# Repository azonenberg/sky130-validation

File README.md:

# sky130 validation stuff

Right now focusing on OpenRAM bringup chip.

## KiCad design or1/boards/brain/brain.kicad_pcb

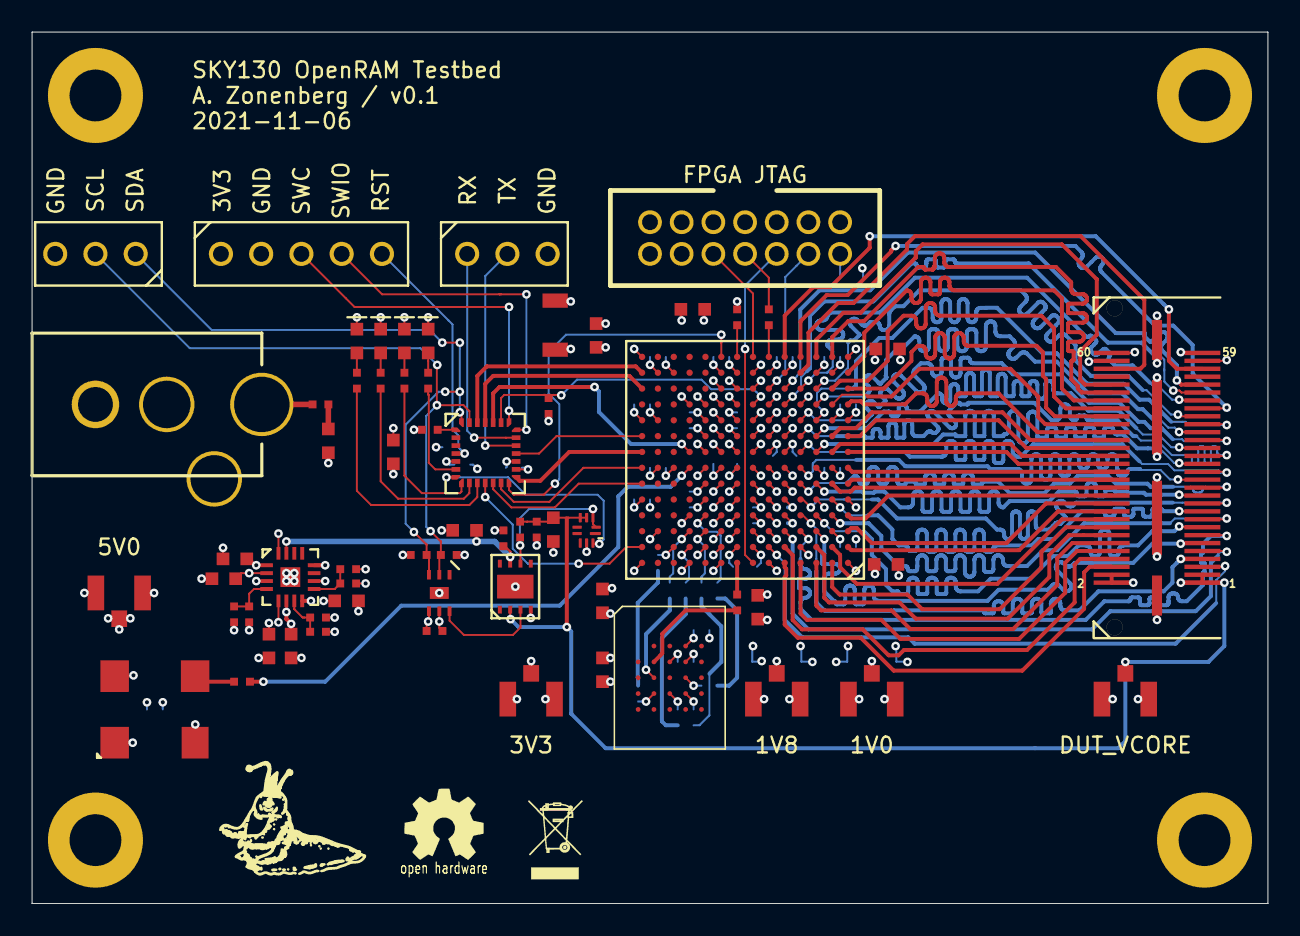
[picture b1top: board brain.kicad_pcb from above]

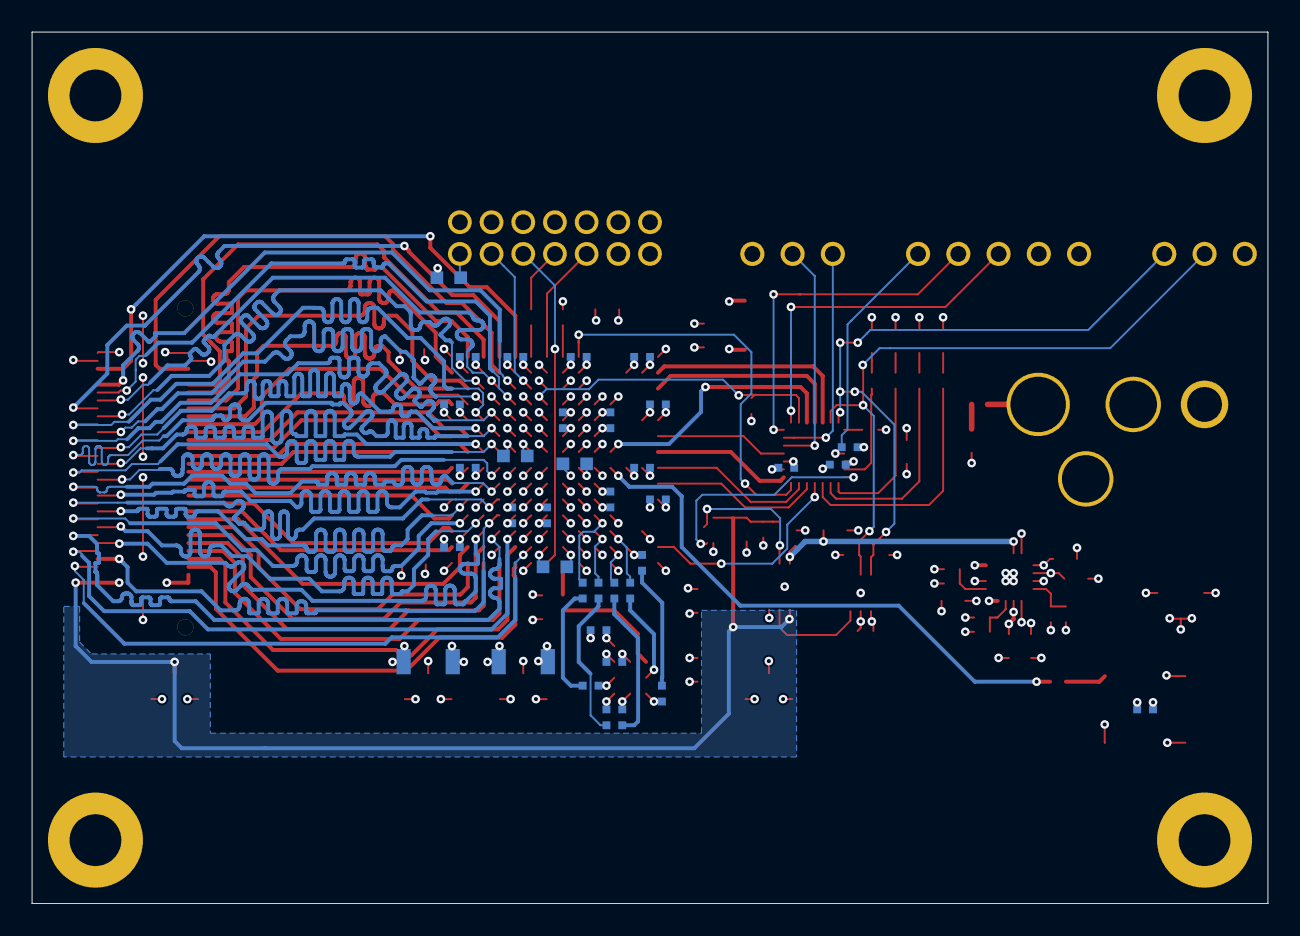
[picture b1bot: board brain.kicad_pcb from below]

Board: 4 copper layers, 78.0 x 55.0 mm, 103 parts (36 on the bottom side), 115 nets.

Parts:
C1, C4: 100 uF; EIA_1206_CAP_NOSILK
C2, C5, C6, C7, C9, C10, C11, C12, C13, C14, C15, C17, C18, C19, C20, C34, C37, C41, C43: 4.7 uF; EIA_0603_CAP_NOSILK
C3: 47 uF; EIA_1206_CAP_NOSILK
C8, C16, C21, C22, C23, C24, C25, C26, C27, C28, C29, C30, C31, C32, C33, C35, C36, C38, C40, C42, C44, C45: 0.47 uF; EIA_0402_CAP_NOSILK
C39: 0.1 uF; EIA_0402_CAP_NOSILK
D1, D2, D3, D4: GREEN; EIA_0603_LED
F1: 1A; EIA_0402_RES_NOSILK
FB1: 600R @ 100 MHz; EIA_0603_INDUCTOR_NOSILK
J1: XILINX_JTAG; XILINX_JTAG_PTH_MOLEX_0878311420
J2: BARREL_JACK; CONN_CUI_PJ-058BH_HIPWR_BARREL_NOSLOT
J3, J6: Conn_01x03; CONN_HEADER_2.54MM_1x3
J4: Conn_01x05; CONN_HEADER_2.54MM_1x5
J5: CONN_SKY130_TEST_HOST; CONN_SAMTEC_QSH-030-01-L-D-A
MH1, MH2, MH3, MH4: SCREWHOLE_4_40; MECHANICAL_CLEARANCEHOLE_4_40
R1, R2: 100K; EIA_0402_RES_NOSILK
R3: 130K; EIA_0402_RES_NOSILK
R4: 49.9K; EIA_0402_RES_NOSILK
R5: 187K; EIA_0402_RES_NOSILK
R6: 33K; EIA_0402_RES_NOSILK
R7, R8, R9, R10, R11, R14, R20, R21, R22, R23, R24, R29: 33; EIA_0402_RES_NOSILK
R12, R25: 10K; EIA_0402_RES_NOSILK
R13, R15, R17, R18: 1K; EIA_0402_RES_NOSILK
R16, R26, R27: 4.7k; EIA_0402_RES_NOSILK
R19: 4.7K; EIA_0402_RES_NOSILK
R28: 10 0.1%; EIA_0402_RES_NOSILK
TP1, TP2, TP3, TP4, TP5: U.FL; CONN_U.FL_TE_1909763-1
U1: STM32F031-QFN28; QFN_28_0.5MM_4x4MM_NOPAD
U2: XC7S15-1FTGB196C; BGA_196_15x15_FULLARRAY_1MM_FTGB196
U3: ADP323; QFN_16_0.5MM_3x3MM
U4: S25FL128SAGBHI300; BGA_24_6x8_DEPOP1_1MM
U5: DAC121C081-WSON; DFN_6_0.65MM_2.2x2.5MM_TI_NGF
U6: ISL24021IRT065Z-T7A‎; DFN_8_0.65MM_3x3MM
U7: INA216A2; QFN_10_0.4MM_1.4x1.8MM_TI_RSW
U8: CB3LV-3C-25M000000; OSCILLATOR_7.0x5.0

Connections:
/1V0: C1.1, C2.1, C6.1, C7.1, C8.1, C15.1, C21.1, C26.1, R1.1, TP4.1, U2.D6, U2.D8, U2.E5, U2.E7, U2.E9, U2.F6, U2.G5, U2.G9, U2.H6, U2.J5, U2.J9, U2.K6, U2.K8, U3.5
/1V8: C3.1, C9.1, C14.1, C16.1, C22.1, R3.1, TP2.1, U2.B8, U2.F8, U2.F10, U2.H10, U2.K10, U2.L9, U3.6
/3V3: C4.1, C10.1, C11.1, C12.1, C17.1, C18.1, C19.1, C20.1, C23.1, C24.1, C25.1, C27.1, C28.1, C29.1, C30.1, C31.1, C32.1, C33.1, C34.1, C35.1, C36.1, C37.1, C38.1, C40.1, C45.1, J1.2, J4.1, J5.57, J5.58, J5.59, J5.60, R5.1, R12.2, R16.1, R19.1, R26.1, R27.1, TP3.1, U1.5, U1.17, U2.B10, U2.G2, U2.G13, U2.K2, U2.K13, U2.M7, U2.N2, U2.N6, U2.N7, U2.N8, U2.N13, U3.8, U4.B4, U5.5, U8.1, U8.4
/DUT socket/ADDR0_0: J5.44, U2.M1
/DUT socket/ADDR0_1: J5.43, U2.M3
/DUT socket/ADDR0_2: J5.41, U2.K3
/DUT socket/ADDR0_3: J5.39, U2.L3
/DUT socket/ADDR0_4: J5.37, U2.K4
/DUT socket/ADDR0_5: J5.35, U2.J3
/DUT socket/ADDR0_6: J5.33, U2.J4
/DUT socket/ADDR0_7: J5.31, U2.H3
/DUT socket/ADDR1_0: J5.13, U2.C4
/DUT socket/ADDR1_1: J5.11, U2.C3
/DUT socket/ADDR1_2: J5.9, U2.C5
/DUT socket/ADDR1_3: J5.7, U2.D4
/DUT socket/ADDR1_4: J5.5, U2.B6
/DUT socket/ADDR1_5: J5.8, U2.B5
/DUT socket/ADDR1_6: J5.12, U2.A3
/DUT socket/ADDR1_7: J5.16, U2.A2
/DUT socket/CLK0: J5.45, U2.P4
/DUT socket/CLK1: J5.55, U2.P5
/DUT socket/CS0_N: J5.46, U2.M2
/DUT socket/CS1_N: J5.56, U2.N4
/DUT socket/DIN0_0: J5.40, U2.L1
/DUT socket/DIN0_1: J5.38, U2.J2
/DUT socket/DIN0_2: J5.32, U2.H1
/DUT socket/DIN0_3: J5.30, U2.G1
/DUT socket/DIN0_4: J5.26, U2.F2
/DUT socket/DIN0_5: J5.22, U2.C1
/DUT socket/DIN0_6: J5.18, U2.B2
/DUT socket/DIN0_7: J5.10, U2.A4
/DUT socket/DOUT0_0: J5.36, U2.J1
/DUT socket/DOUT0_1: J5.42, U2.L2
/DUT socket/DOUT0_2: J5.34, U2.H2
/DUT socket/DOUT0_3: J5.28, U2.F1
/DUT socket/DOUT0_4: J5.24, U2.D1
/DUT socket/DOUT0_5: J5.20, U2.B1
/DUT socket/DOUT0_6: J5.14, U2.B3
/DUT socket/DOUT0_7: J5.6, U2.A5
/DUT socket/DOUT1_0: J5.15, U2.D3
/DUT socket/DOUT1_1: J5.27, U2.G4
/DUT socket/DOUT1_2: J5.29, U2.H4
/DUT socket/DOUT1_3: J5.17, U2.D2
/DUT socket/DOUT1_4: J5.19, U2.E2
/DUT socket/DOUT1_5: J5.21, U2.E4
/DUT socket/DOUT1_6: J5.23, U2.F3
/DUT socket/DOUT1_7: J5.25, U2.F4
/DUT socket/GPIO0: J5.52, U2.P3
/DUT socket/WE0_N: J5.50, U2.P2
/DUT socket/WMASK0_0: J5.51, U2.M5
/DUT socket/WMASK0_1: J5.49, U2.L5
/DUT socket/WMASK0_2: J5.47, U2.M4
/DUT socket/WMASK0_3: J5.48, U2.N1
/DUT_VCORE: C43.1, C44.1, J5.1, J5.2, J5.3, J5.4, R28.1, TP5.1, U6.2, U7.4, U7.5
/DUT_VDD_ISENSE: U1.7, U7.10
/FLASH_CS_N: R11.2, U4.C2
/FLASH_DQ0: R7.2, R21.1
/FLASH_DQ1: R8.2, R22.1
/FLASH_DQ2: R9.2, R23.1
/FLASH_DQ3: R10.2, R24.1
/FLASH_RST_N: R12.1, U4.A4
/FLASH_SCK: R20.1, U4.B2
/FPGA_CLK_25MHZ: R29.1, U2.G11
/FPGA_DONE: U1.14, U2.P9
/FPGA_RST_N: R16.2, U1.23, U2.L7
/GND: C1.2, C2.2, C3.2, C4.2, C5.2, C6.2, C7.2, C8.2, C9.2, C10.2, C11.2, C12.2, C13.2, C14.2, C15.2, C16.2, C17.2, C18.2, C19.2, C20.2, C21.2, C22.2, C23.2, C24.2, C25.2, C26.2, C27.2, C28.2, C29.2, C30.2, C31.2, C32.2, C33.2, C34.2, C35.2, C36.2, C37.2, C38.2, C39.2, C40.2, C41.2, C42.2, C43.2, C44.2, C45.2, D1.1, D2.1, D3.1, D4.1, J1.3, J1.5, J1.7, J1.9, J1.11, J2.2, J3.3, J4.2, J5.GND, J6.3, R2.1, R4.1, R6.1, R25.2, TP1.2, TP2.2, TP3.2, TP4.2, TP5.2, U1.16, U2.A1, U2.A6, U2.A9, U2.A11, U2.A14, U2.B4, U2.B7, U2.B9, U2.C2, U2.C6, U2.C7, U2.C8, U2.C9, U2.C13, U2.D5, U2.D7, U2.D9, U2.D11, U2.E1, U2.E3, U2.E6, U2.E8, U2.E10, U2.E14, U2.F5, U2.F7, U2.F9, U2.G3, U2.G6, U2.G7, U2.G8, U2.G10, U2.G12, U2.H5, U2.H7, U2.H8, U2.H9, U2.J6, U2.J7, U2.J8, U2.J10, U2.K1, U2.K5, U2.K7, U2.K9, U2.K14, U2.L4, U2.L6, U2.L8, U2.L10, U2.L11, U2.M8, U2.M9, U2.N3, U2.N5, U2.N9, U2.N12, U2.P1, U2.P14, U3.12, U3.PAD, U4.B3, U5.4, U5.PAD, U6.4, U6.PAD, U7.9, U8.2
/I2C_SCL: J6.2, R26.2, U1.27, U5.2
/I2C_SDA: J6.1, R27.2, U1.28, U5.3
/JTAG_TCK: J1.6, U2.A7
/JTAG_TDI: J1.10, U2.P7
/JTAG_TDO: J1.8, R14.2
/JTAG_TMS: J1.4, U2.M6
/MCU_GPIO0: U1.12, U2.F14
/MCU_GPIO1: U1.13, U2.G14
/MCU_GPIO2: U1.18, U2.J14
/MCU_GPIO3: U1.11, U2.B14
/MCU_LED0: R13.2, U1.10
/MCU_LED1: R15.2, U1.9
/MCU_LED2: R17.2, U1.8
/MCU_LED3: R18.2, U1.6
/MCU_RST_N: C39.1, J4.5, U1.4
/MCU_SPI_CS_N: U1.15, U2.H14
/MCU_SPI_SCK: U1.24, U2.H11
/MCU_SPI_SI: U1.26, U2.N14
/MCU_SPI_SO: U1.25, U2.M14
/Power supply/5V0: C5.1, C13.1, C41.1, C42.1, FB1.2, TP1.1, U3.1, U3.2, U3.3, U3.10, U3.15, U3.16, U6.7
/Power supply/DAC_VOUT: U5.6, U6.3
/Power supply/DUT_VDD_RAW: R28.2, U6.6, U7.2, U7.3
/Power supply/MCU_BOOT0: R25.1, U1.1
/SWCLK: J4.3, U1.22
/SWDIO: J4.4, U1.21
/UART_RX: J3.1, U1.20
/UART_TX: J3.2, U1.19
unnamed: D1.2, R13.1
unnamed: D2.2, R15.1
unnamed: D3.2, R17.1
unnamed: D4.2, R18.1
unnamed: F1.1, J2.1
unnamed: F1.2, FB1.1
unnamed: R1.2, R2.2, U3.4
unnamed: R3.2, R4.2, U3.7
unnamed: R5.2, R6.2, U3.9
unnamed: R7.1, U2.B11
unnamed: R8.1, U2.B12
unnamed: R9.1, U2.D10
unnamed: R10.1, U2.C10
unnamed: R11.1, U2.C11
unnamed: R14.1, U2.P6
unnamed: R19.2, U2.P8
unnamed: R20.2, U2.A8
unnamed: R21.2, U4.D3
unnamed: R22.2, U4.D2
unnamed: R23.2, U4.C4
unnamed: R24.2, U4.D4
unnamed: R29.2, U8.3

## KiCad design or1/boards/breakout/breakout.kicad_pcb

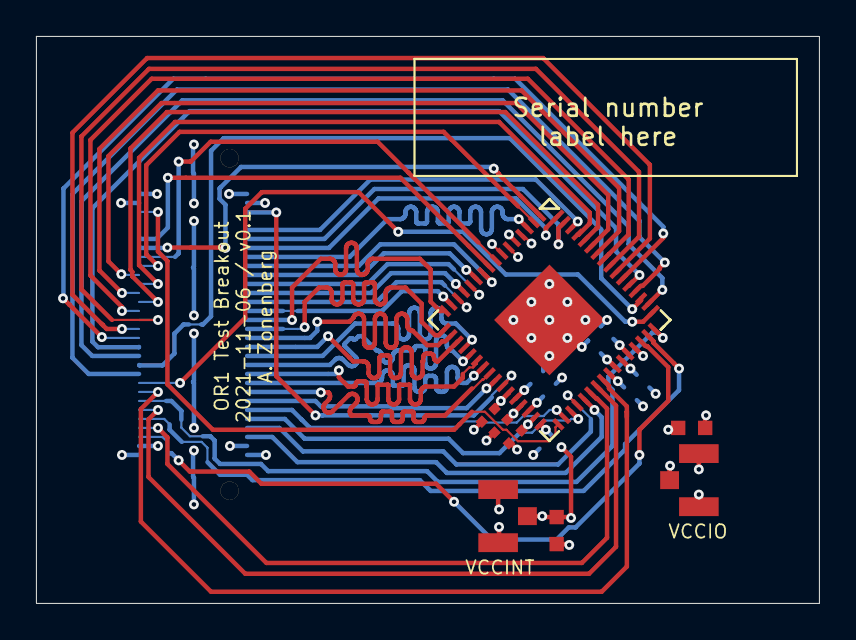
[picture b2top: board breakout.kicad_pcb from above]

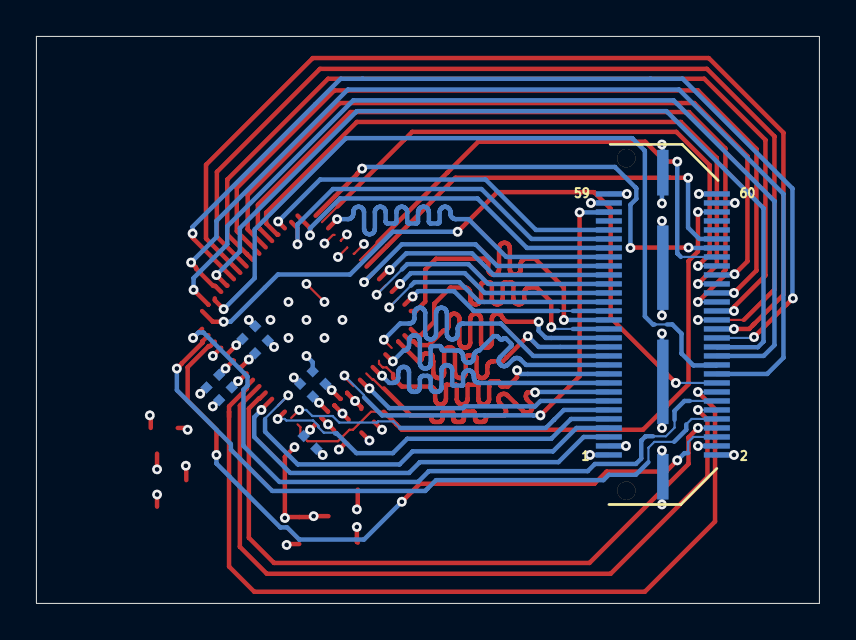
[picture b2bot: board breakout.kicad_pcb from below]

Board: 4 copper layers, 43.5 x 31.5 mm, 16 parts (8 on the bottom side), 52 nets.

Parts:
C1, C2: 4.7 uF; EIA_0603_CAP_NOSILK
C3, C4, C5, C6, C7, C8, C9, C10, C11, C12: 0.47 uF; EIA_0402_CAP_NOSILK
J1: CONN_SKY130_TEST_DEVICE; CONN_SAMTEC_QTH-030-01-L-D-A
TP1, TP2: U.FL; CONN_U.FL_TE_1909763-1
U1: SKY130_TEST_OR1; QFN_64_0.5MM_9x9MM

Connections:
/ADDR0[0]: J1.44, U1.2
/ADDR0[1]: J1.43, U1.10
/ADDR0[2]: J1.41, U1.11
/ADDR0[3]: J1.39, U1.12
/ADDR0[4]: J1.37, U1.13
/ADDR0[5]: J1.35, U1.14
/ADDR0[6]: J1.33, U1.15
/ADDR0[7]: J1.31, U1.16
/ADDR1[0]: J1.13, U1.25
/ADDR1[1]: J1.11, U1.34
/ADDR1[2]: J1.9, U1.35
/ADDR1[3]: J1.7, U1.36
/ADDR1[4]: J1.5, U1.37
/ADDR1[5]: J1.8, U1.38
/ADDR1[6]: J1.12, U1.39
/ADDR1[7]: J1.16, U1.40
/CLK0: J1.45, U1.3
/CLK1: J1.55, U1.26
/CS0_N: J1.46, U1.8
/CS1_N: J1.56, U1.33
/DIN0[0]: J1.40, U1.61
/DIN0[7]: J1.38, U1.58
/DIN0[8]: J1.32, U1.56
/DIN0[15]: J1.30, U1.55
/DIN0[16]: J1.26, U1.53
/DIN0[23]: J1.22, U1.51
/DIN0[24]: J1.18, U1.49
/DIN0[31]: J1.10, U1.47
/DOUT0[0]: J1.36, U1.60
/DOUT0[7]: J1.42, U1.59
/DOUT0[8]: J1.34, U1.57
/DOUT0[15]: J1.28, U1.54
/DOUT0[16]: J1.20, U1.52
/DOUT0[23]: J1.24, U1.50
/DOUT0[24]: J1.14, U1.48
/DOUT0[31]: J1.6, U1.46
/DOUT1[0]: J1.15, U1.24
/DOUT1[7]: J1.27, U1.18
/DOUT1[8]: J1.29, U1.17
/DOUT1[15]: J1.17, U1.23
/DOUT1[16]: J1.19, U1.22
/DOUT1[23]: J1.21, U1.21
/DOUT1[24]: J1.23, U1.20
/DOUT1[31]: J1.25, U1.19
/GND: C1.2, C2.2, C3.2, C4.2, C5.2, C6.2, C7.2, C8.2, C9.2, C10.2, C11.2, C12.2, J1.GND, TP1.2, TP2.2, U1.4, U1.5, U1.6, U1.7, U1.45, U1.PAD
/VCCINT: C2.1, C4.1, C6.1, C8.1, C10.1, C12.1, J1.1, J1.2, J1.3, J1.4, TP2.1, U1.28, U1.29, U1.30, U1.31, U1.32
/VCCIO: C1.1, C3.1, C5.1, C7.1, C9.1, C11.1, J1.57, J1.58, J1.59, J1.60, TP1.1, U1.27, U1.41, U1.42, U1.43, U1.44
/WE0_N: J1.50, U1.9
/WMASK0[0]: J1.51, U1.62
/WMASK0[1]: J1.49, U1.63
/WMASK0[2]: J1.47, U1.64
/WMASK0[3]: J1.48, U1.1

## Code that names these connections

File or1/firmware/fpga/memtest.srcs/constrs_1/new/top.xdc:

set_property IOSTANDARD LVCMOS33 [get_ports {addr0[7]}]
set_property IOSTANDARD LVCMOS33 [get_ports {addr0[6]}]
set_property IOSTANDARD LVCMOS33 [get_ports {addr0[5]}]
set_property IOSTANDARD LVCMOS33 [get_ports {addr0[4]}]
set_property IOSTANDARD LVCMOS33 [get_ports {addr0[3]}]
set_property IOSTANDARD LVCMOS33 [get_ports {addr0[2]}]
set_property IOSTANDARD LVCMOS33 [get_ports {addr0[1]}]
set_property IOSTANDARD LVCMOS33 [get_ports {addr0[0]}]
set_property IOSTANDARD LVCMOS33 [get_ports {addr1[7]}]
set_property IOSTANDARD LVCMOS33 [get_ports {addr1[6]}]
set_property IOSTANDARD LVCMOS33 [get_ports {addr1[5]}]
set_property IOSTANDARD LVCMOS33 [get_ports {addr1[4]}]
set_property IOSTANDARD LVCMOS33 [get_ports {addr1[3]}]
set_property IOSTANDARD LVCMOS33 [get_ports {addr1[2]}]
set_property IOSTANDARD LVCMOS33 [get_ports {addr1[1]}]
set_property IOSTANDARD LVCMOS33 [get_ports {addr1[0]}]
set_property IOSTANDARD LVCMOS33 [get_ports {flash_dq[3]}]
set_property IOSTANDARD LVCMOS33 [get_ports {flash_dq[2]}]
set_property IOSTANDARD LVCMOS33 [get_ports {flash_dq[1]}]
set_property IOSTANDARD LVCMOS33 [get_ports {flash_dq[0]}]
set_property IOSTANDARD LVCMOS33 [get_ports {mcu_gpio[3]}]
set_property IOSTANDARD LVCMOS33 [get_ports {mcu_gpio[2]}]
set_property IOSTANDARD LVCMOS33 [get_ports {mcu_gpio[1]}]
set_property IOSTANDARD LVCMOS33 [get_ports {mcu_gpio[0]}]
set_property IOSTANDARD LVCMOS33 [get_ports {rdata0[7]}]
set_property IOSTANDARD LVCMOS33 [get_ports {rdata0[6]}]
set_property IOSTANDARD LVCMOS33 [get_ports {rdata0[5]}]
set_property IOSTANDARD LVCMOS33 [get_ports {rdata0[4]}]
set_property IOSTANDARD LVCMOS33 [get_ports {rdata0[3]}]
set_property IOSTANDARD LVCMOS33 [get_ports {rdata0[2]}]
set_property IOSTANDARD LVCMOS33 [get_ports {rdata0[1]}]
set_property IOSTANDARD LVCMOS33 [get_ports {rdata0[0]}]
set_property IOSTANDARD LVCMOS33 [get_ports {rdata1[7]}]
set_property IOSTANDARD LVCMOS33 [get_ports {rdata1[6]}]
set_property IOSTANDARD LVCMOS33 [get_ports {rdata1[5]}]
set_property IOSTANDARD LVCMOS33 [get_ports {rdata1[4]}]
set_property IOSTANDARD LVCMOS33 [get_ports {rdata1[3]}]
set_property IOSTANDARD LVCMOS33 [get_ports {rdata1[2]}]
set_property IOSTANDARD LVCMOS33 [get_ports {rdata1[1]}]
set_property IOSTANDARD LVCMOS33 [get_ports {rdata1[0]}]
set_property IOSTANDARD LVCMOS33 [get_ports {wdata0[7]}]
set_property IOSTANDARD LVCMOS33 [get_ports {wdata0[6]}]
set_property IOSTANDARD LVCMOS33 [get_ports {wdata0[5]}]
set_property IOSTANDARD LVCMOS33 [get_ports {wdata0[4]}]
set_property IOSTANDARD LVCMOS33 [get_ports {wdata0[3]}]
set_property IOSTANDARD LVCMOS33 [get_ports {wdata0[2]}]
set_property IOSTANDARD LVCMOS33 [get_ports {wdata0[1]}]
set_property IOSTANDARD LVCMOS33 [get_ports {wdata0[0]}]
set_property IOSTANDARD LVCMOS33 [get_ports {wmask0[3]}]
set_property IOSTANDARD LVCMOS33 [get_ports {wmask0[2]}]
set_property IOSTANDARD LVCMOS33 [get_ports {wmask0[1]}]
set_property IOSTANDARD LVCMOS33 [get_ports {wmask0[0]}]
set_property IOSTANDARD LVCMOS33 [get_ports clk0]
set_property IOSTANDARD LVCMOS33 [get_ports clk1]
set_property IOSTANDARD LVCMOS33 [get_ports clk_25mhz]
set_property IOSTANDARD LVCMOS33 [get_ports cs0_n]
set_property IOSTANDARD LVCMOS33 [get_ports dut_gpio0]
set_property IOSTANDARD LVCMOS33 [get_ports cs1_n]
set_property IOSTANDARD LVCMOS33 [get_ports flash_cs_n]
set_property IOSTANDARD LVCMOS33 [get_ports mcu_spi_cs_n]
set_property IOSTANDARD LVCMOS33 [get_ports mcu_spi_sck]
set_property IOSTANDARD LVCMOS33 [get_ports mcu_spi_si]
set_property IOSTANDARD LVCMOS33 [get_ports mcu_spi_so]
set_property IOSTANDARD LVCMOS33 [get_ports we0_n]
set_property PACKAGE_PIN C3 [get_ports {addr1[1]}]
set_property PACKAGE_PIN A3 [get_ports {addr1[6]}]
set_property PACKAGE_PIN B5 [get_ports {addr1[5]}]
set_property PACKAGE_PIN C5 [get_ports {addr1[2]}]
set_property PACKAGE_PIN D4 [get_ports {addr1[3]}]
set_property PACKAGE_PIN B6 [get_ports {addr1[4]}]
set_property PACKAGE_PIN A2 [get_ports {addr1[7]}]
set_property PACKAGE_PIN C4 [get_ports {addr1[0]}]
set_property PACKAGE_PIN H3 [get_ports {addr0[7]}]
set_property PACKAGE_PIN J4 [get_ports {addr0[6]}]
set_property PACKAGE_PIN J3 [get_ports {addr0[5]}]
set_property PACKAGE_PIN K4 [get_ports {addr0[4]}]
set_property PACKAGE_PIN L3 [get_ports {addr0[3]}]
set_property PACKAGE_PIN K3 [get_ports {addr0[2]}]
set_property PACKAGE_PIN M3 [get_ports {addr0[1]}]
set_property PACKAGE_PIN M1 [get_ports {addr0[0]}]
set_property PACKAGE_PIN C10 [get_ports {flash_dq[3]}]
set_property PACKAGE_PIN D10 [get_ports {flash_dq[2]}]
set_property PACKAGE_PIN B12 [get_ports {flash_dq[1]}]
set_property PACKAGE_PIN B11 [get_ports {flash_dq[0]}]
set_property PACKAGE_PIN B14 [get_ports {mcu_gpio[3]}]
set_property PACKAGE_PIN J14 [get_ports {mcu_gpio[2]}]
set_property PACKAGE_PIN G14 [get_ports {mcu_gpio[1]}]
set_property PACKAGE_PIN F14 [get_ports {mcu_gpio[0]}]
set_property PACKAGE_PIN A5 [get_ports {rdata0[7]}]
set_property PACKAGE_PIN B3 [get_ports {rdata0[6]}]
set_property PACKAGE_PIN D1 [get_ports {rdata0[5]}]
set_property PACKAGE_PIN B1 [get_ports {rdata0[4]}]
set_property PACKAGE_PIN F1 [get_ports {rdata0[3]}]
set_property PACKAGE_PIN H2 [get_ports {rdata0[2]}]
set_property PACKAGE_PIN L2 [get_ports {rdata0[1]}]
set_property PACKAGE_PIN J1 [get_ports {rdata0[0]}]
set_property PACKAGE_PIN F4 [get_ports {rdata1[7]}]
set_property PACKAGE_PIN F3 [get_ports {rdata1[6]}]
set_property PACKAGE_PIN E4 [get_ports {rdata1[5]}]
set_property PACKAGE_PIN E2 [get_ports {rdata1[4]}]
set_property PACKAGE_PIN D2 [get_ports {rdata1[3]}]
set_property PACKAGE_PIN H4 [get_ports {rdata1[2]}]
set_property PACKAGE_PIN G4 [get_ports {rdata1[1]}]
set_property PACKAGE_PIN D3 [get_ports {rdata1[0]}]
set_property PACKAGE_PIN A4 [get_ports {wdata0[7]}]
set_property PACKAGE_PIN B2 [get_ports {wdata0[6]}]
set_property PACKAGE_PIN C1 [get_ports {wdata0[5]}]
set_property PACKAGE_PIN F2 [get_ports {wdata0[4]}]
set_property PACKAGE_PIN G1 [get_ports {wdata0[3]}]
set_property PACKAGE_PIN H1 [get_ports {wdata0[2]}]
set_property PACKAGE_PIN J2 [get_ports {wdata0[1]}]
set_property PACKAGE_PIN L1 [get_ports {wdata0[0]}]
set_property PACKAGE_PIN N1 [get_ports {wmask0[3]}]
set_property PACKAGE_PIN M4 [get_ports {wmask0[2]}]
set_property PACKAGE_PIN L5 [get_ports {wmask0[1]}]
set_property PACKAGE_PIN M5 [get_ports {wmask0[0]}]
set_property PACKAGE_PIN P4 [get_ports clk0]
set_property PACKAGE_PIN P5 [get_ports clk1]
set_property PACKAGE_PIN M2 [get_ports cs0_n]
set_property PACKAGE_PIN N4 [get_ports cs1_n]
set_property PACKAGE_PIN P3 [get_ports dut_gpio0]
set_property PACKAGE_PIN P2 [get_ports we0_n]
set_property PACKAGE_PIN G11 [get_ports clk_25mhz]
set_property PACKAGE_PIN C11 [get_ports flash_cs_n]
set_property PACKAGE_PIN H14 [get_ports mcu_spi_cs_n]
set_property PACKAGE_PIN H11 [get_ports mcu_spi_sck]
set_property PACKAGE_PIN N14 [get_ports mcu_spi_si]
set_property PACKAGE_PIN M14 [get_ports mcu_spi_so]

create_clock -period 40.000 -name clk_25mhz -waveform {0.000 20.000} [get_ports clk_25mhz]

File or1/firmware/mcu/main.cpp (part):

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	led3 = 0;

	//Initialize the UART
	static GPIOPin uart_tx(&GPIOA, 9,	GPIOPin::MODE_PERIPHERAL, 1);
	static GPIOPin uart_rx(&GPIOA, 10, GPIOPin::MODE_PERIPHERAL, 1);
	static UART uart(&USART1, &USART1, 417);
	g_uart = &uart;

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
	//Initialize FPGA status pins
	g_log("Releasing FPGA reset\n");
	static GPIOPin fpga_rst_n(&GPIOA, 15, GPIOPin::MODE_OUTPUT);
	static GPIOPin fpga_done(&GPIOB, 0, GPIOPin::MODE_INPUT);
	fpga_rst_n = 1;

	//Initialize CLI
	g_uartStream.Initialize(g_uart);
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	//Set up I2C.
	//Prescale divide by 8 (6 MHz, 166.6 ns/tick)
	//Divide I2C clock by 16 after that to get 375 kHz
	static GPIOPin i2c_sda( &GPIOB, 7, GPIOPin::MODE_PERIPHERAL, 1);
	static GPIOPin i2c_scl( &GPIOB, 6, GPIOPin::MODE_PERIPHERAL, 1);
	static I2C i2c(&I2C1, 8, 8);
	g_i2c = &i2c;

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
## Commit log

2021-06-23 Initial version of schematic ready for design review
2021-08-08 Continued initial work on brain board
2021-08-08 Updated brain board with silkscreen logos and mounting holes
2021-08-15 Initial version of breakout
2021-11-05 Finished initial routing. Ready for layout review.
2021-11-06 Final rev of breakout ready for fab
2021-11-06 Final rev of brain after layout review
2021-11-06 Initial crosstalk and plane crossing sims for breakout
2021-11-22 Initial MCU firmware for configuring DAC
2021-11-22 Added CLI session and interrupt vector file missed in last commit
2021-11-22 Initial skeleton FPGA firmware
2021-12-09 Continued work on memory test RTL
2021-12-09 MemoryTester now gives correct, expected results on both ports for a single PRBS test on one die
2021-12-16 Continued work on memory test code
2021-12-28 Initial characterization data
2021-12-28 Updated memory test firmware
2022-01-01 Initial implementation of fvshmoo test
2022-01-01 Uploading characterization data to date
2022-01-01 Added die 1 fvshmoo characterization data
2022-01-01 Fixed bug in summarization script
2022-01-02 Added pipeline register in IOB for read capture
2022-01-02 Read capture now uses a pipeline register in a separate clock domain to optimize capture window
2022-01-02 Fixed typo in log messages
2022-01-02 Added static phase delay to fvshmoo to compensate for PCB trace delays
2022-01-02 Added fpshmoo
2022-01-02 fvshmoo now runs to 45 MHz and uses optimized 11ns read capture delay
2022-01-02 Removed out of date spreadsheets
2022-01-02 New test results from fvshmoo with optimized read capture delay
2022-01-02 Added die 1 summary with new timing
2022-01-02 Added test data from dies 2 and 3
2022-01-07 Added vmap
2022-01-07 Added vmap test results on die 1
2022-01-07 Added data from die 2 vmap, rearranged some stuff
2022-01-08 Added die 3 vmap analysis
2022-01-08 Added die 3 vmap raw data
2022-01-08 Added source and data for rwshmoo test
2022-01-09 Use different synchronization strategy to ensure that reads/writes intended to be simultaneous start exactly the same cycle
2022-01-09 MemoryTester: added IOB registers for all outputs to improve timing repeatability
2022-01-09 Registered all FPGA I/Os for more repeatable timing
2022-01-09 Updated characterization data for rwshmoo test with bug fixes on FPGA side
2022-01-09 Removed operating voltage test results as they're redundant (duplicated by shmoo plots)
2022-01-09 Added characterization data from die 5
2022-01-09 Added more characterization data from die 5
2022-01-10 Added characterization data from die 4
2022-01-10 Added die 3 characterization data
2022-01-10 Unified frequency/sampling delay time for everything. Updated CLI library with bug fix.
2022-01-10 Updated CLI library again with more bug fixes
2022-01-10 Added characterization data from die 2
2022-01-10 Added some missing test data
2022-01-10 Added characterization data from die 1
2022-01-11 Added analysis for fpshmoo
2022-01-11 Added die 5 single port heated plot
2022-01-11 Added fvshmoo analysis
2022-01-11 Added retention analysis
2022-01-11 Added rwshmoo analysis
2022-01-11 Added rearranged vmap data
2022-01-11 Added small vmap images
2022-01-11 Added large vmap images

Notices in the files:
or1/firmware/mcu/main.cpp:
Copyright (c) 2021 Andrew D. Zonenberg
All rights reserved.
